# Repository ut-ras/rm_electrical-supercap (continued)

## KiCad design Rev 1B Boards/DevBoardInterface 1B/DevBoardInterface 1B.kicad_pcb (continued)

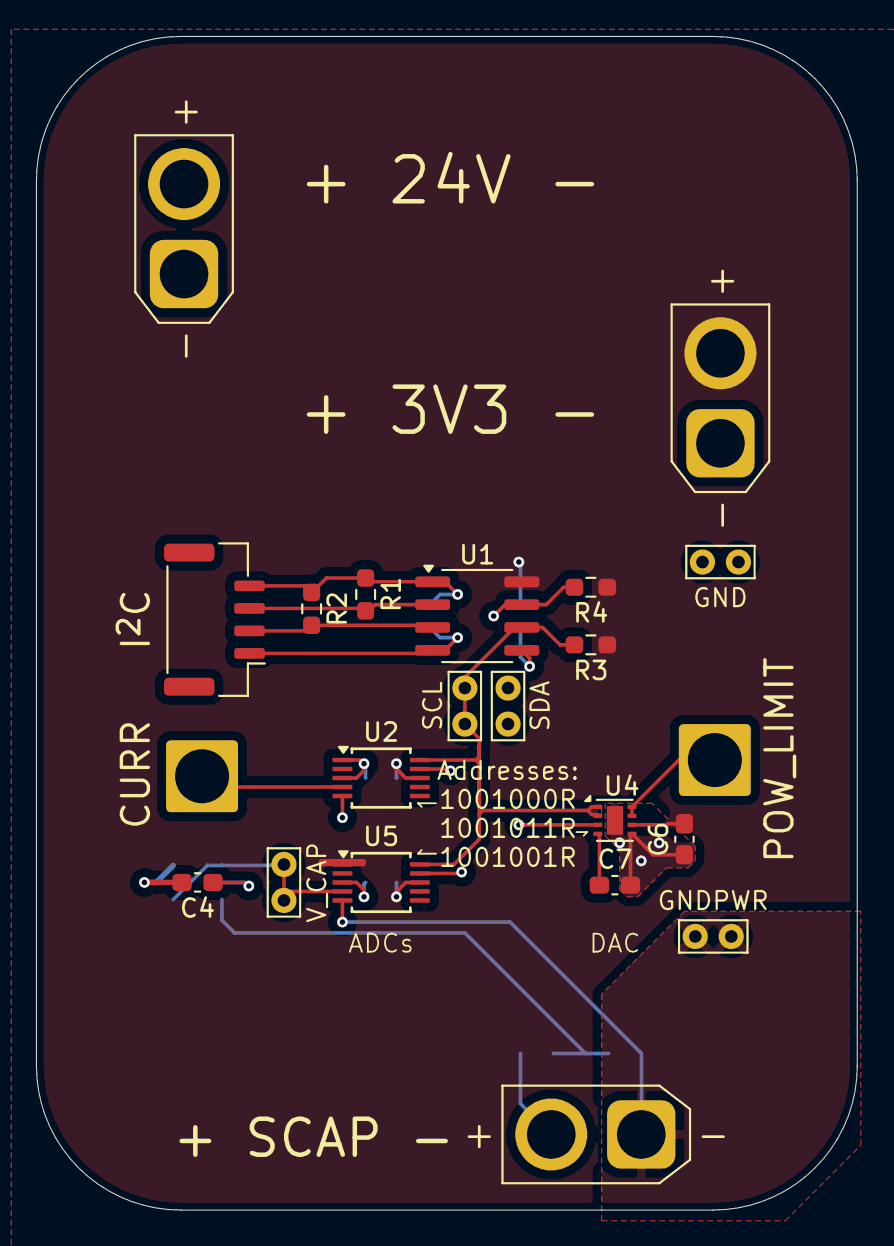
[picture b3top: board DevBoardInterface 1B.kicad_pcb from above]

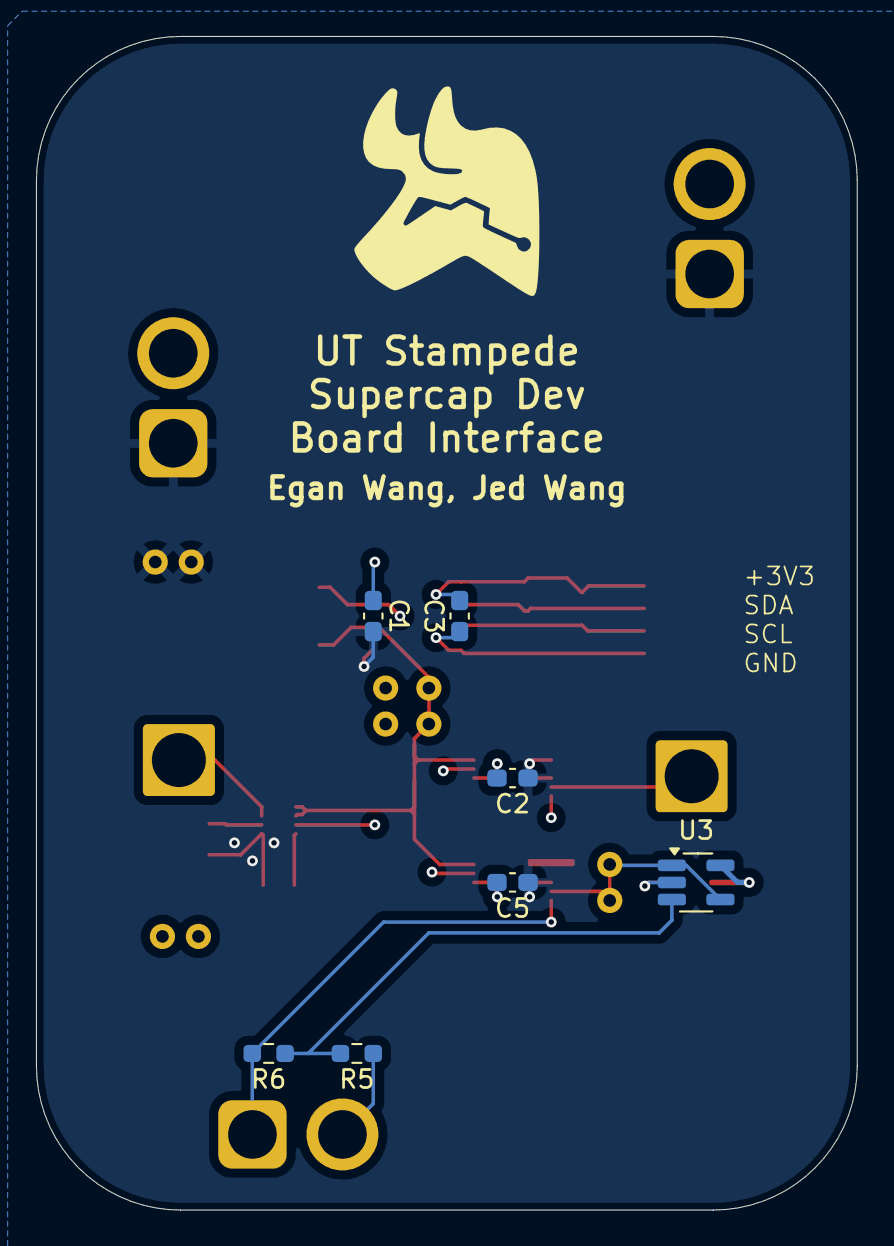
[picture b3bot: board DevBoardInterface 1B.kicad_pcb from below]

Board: 4 copper layers, 45.6 x 65.2 mm, 29 parts (7 on the bottom side), 16 nets.

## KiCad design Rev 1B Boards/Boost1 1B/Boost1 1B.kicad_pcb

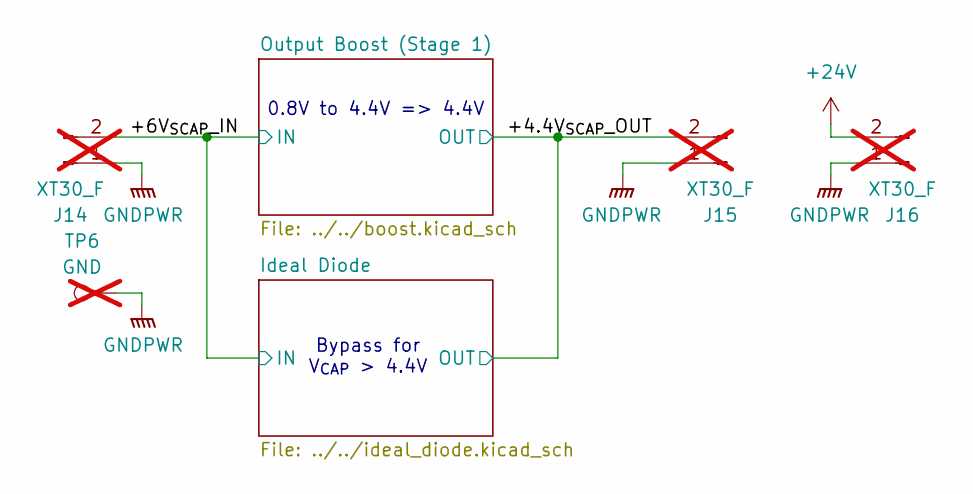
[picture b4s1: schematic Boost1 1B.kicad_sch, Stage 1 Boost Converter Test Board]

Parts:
J14, J15, J16: XT30_F; AMASS_XT30U-F_1x02_P5.0mm_Vertical; not fitted
TP6: GND; TestPoint_Bridge_Pitch2.0mm_Drill0.7mm; not fitted

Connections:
+24V: J16.2; also elsewhere on the board
/+4.4V_{SCAP}_OUT: J15.2; also elsewhere on the board
/+6V_{SCAP}_IN: J14.2; also elsewhere on the board
GNDPWR: J14.1, J15.1, J16.1, TP6.1; also elsewhere on the board

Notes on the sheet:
0.8V to 4.4V => 4.4V
Bypass for V_{CAP} > 4.4V

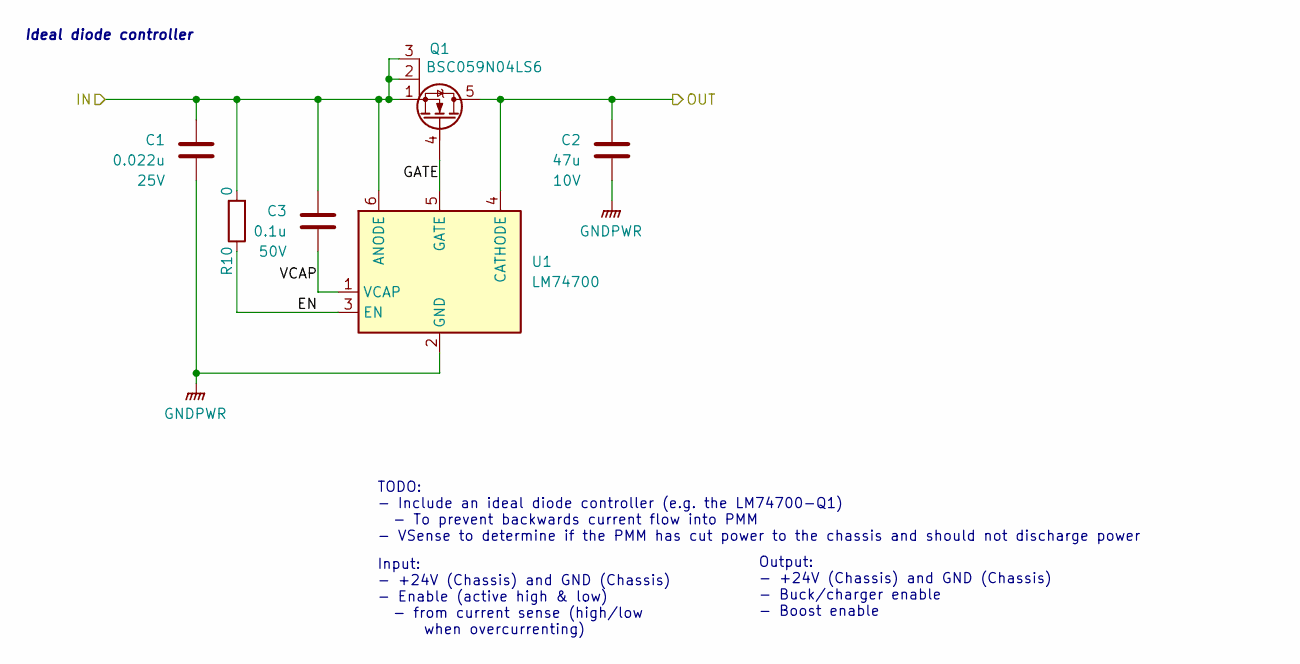
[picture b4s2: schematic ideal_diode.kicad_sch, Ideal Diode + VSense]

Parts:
C1: 0.022u; C_0603_1608Metric_Pad1.08x0.95mm_HandSolder; Voltage Rating 25V; Mouser Part Number 710-885012206067
C2: 47u; C_1206_3216Metric_Pad1.33x1.80mm_HandSolder; Voltage Rating 10V; Mouser Part Number 81-GRM31CR61A476ME5K
C3: 0.1u; C_0603_1608Metric_Pad1.08x0.95mm_HandSolder; Voltage Rating 50V; Mouser Part Number 581-KGM15BR71H104JT
Q1: BSC059N04LS6; Infineon_PG-TDSON-8_6.15x5.15mm; Mouser Part Number 726-BSC059N04LS6ATMA
R10: 0; R_0603_1608Metric_Pad0.98x0.95mm_HandSolder; Mouser Part Number 660-RK73Z1JTTDD
U1: LM74700; SOT-23-6_Handsoldering; Mouser Part Number 595-LM74700QDBVRQ1

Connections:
/+4.4V_{SCAP}_OUT: C2.1, Q1.5 (D), U1.4 (CATHODE); also elsewhere on the board
/+6V_{SCAP}_IN: C1.1, C3.1, Q1.1 (S), Q1.2 (S), Q1.3 (S), R10.2, U1.6 (ANODE); also elsewhere on the board
/Ideal Diode/EN: R10.1, U1.3 (EN)
/Ideal Diode/GATE: Q1.4 (G), U1.5 (GATE)
/Ideal Diode/VCAP: C3.2, U1.1 (VCAP)
GNDPWR: C1.2, C2.2, U1.2 (GND); also elsewhere on the board

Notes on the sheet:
Input: - +24V (Chassis) and GND (Chassis) - Enable (active high & low) - from current sense (high/low when overcurrenting)
Ideal diode controller
Output: - +24V (Chassis) and GND (Chassis) - Buck/charger enable - Boost enable
TODO: - Include an ideal diode controller (e.g. the LM74700-Q1) - To prevent backwards current flow into PMM - VSense to determine if the PMM has cut power to the chassis and should not discharge power

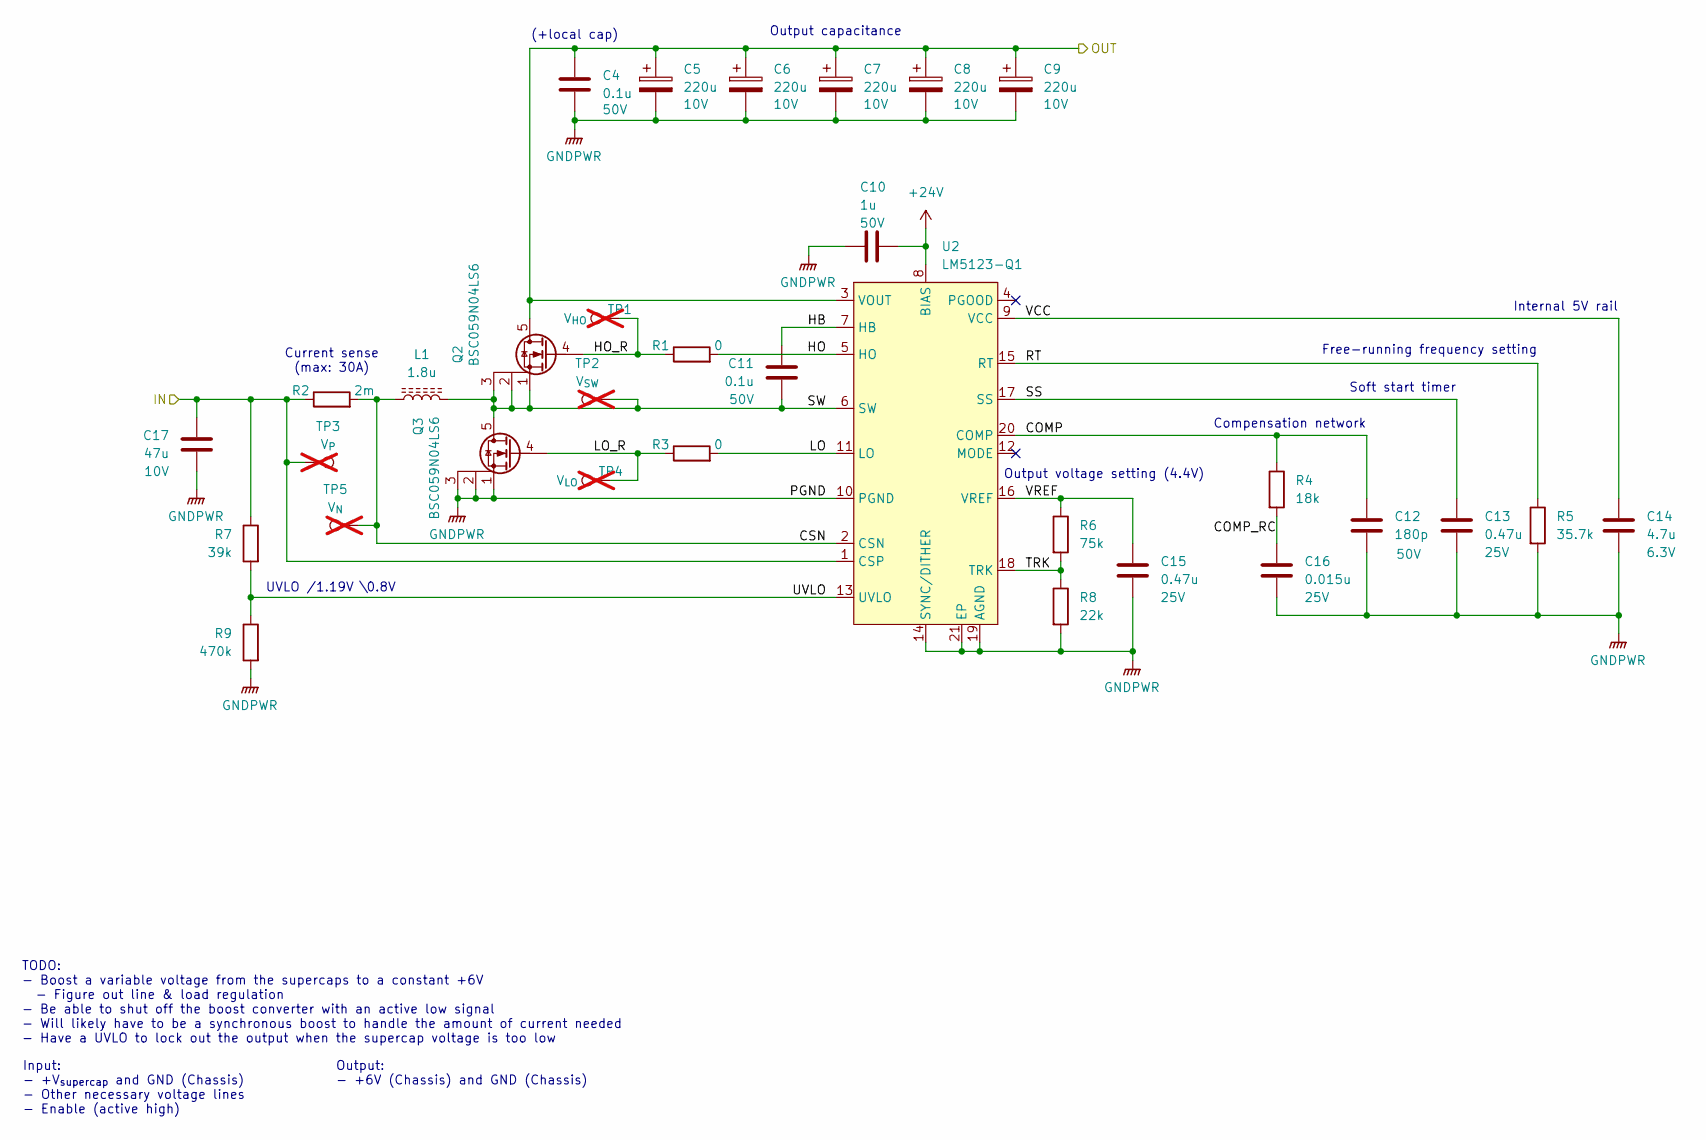
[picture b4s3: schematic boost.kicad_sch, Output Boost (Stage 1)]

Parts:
C4, C11: 0.1u; C_0603_1608Metric_Pad1.08x0.95mm_HandSolder; Voltage Rating 50V; Mouser Part Number 581-KGM15BR71H104JT
C5, C6, C7, C8, C9: 220u; CP_Radial_D6.3mm_P2.50mm; Voltage Rating 10V; Mouser Part Number 80-A750EK227M1AAAE18
C10: 1u; C_0603_1608Metric_Pad1.08x0.95mm_HandSolder; Voltage Rating 50V; Mouser Part Number 963-UMK107BJ105KA-T
C12: 180p; C_0603_1608Metric_Pad1.08x0.95mm_HandSolder; Voltage Rating 50V; Mouser Part Number 603-CC603JPNPO9BN181
C13, C15: 0.47u; C_0603_1608Metric_Pad1.08x0.95mm_HandSolder; Voltage Rating 25V; Mouser Part Number 710-885012106020
C14: 4.7u; C_0603_1608Metric_Pad1.08x0.95mm_HandSolder; Voltage Rating 6.3V; Mouser Part Number 187-CL10A475KQ8NNWC
C16: 0.015u; C_0603_1608Metric_Pad1.08x0.95mm_HandSolder; Voltage Rating 25V; Mouser Part Number 77-VJ0603Y153KXXCBC
C17: 47u; C_1206_3216Metric_Pad1.33x1.80mm_HandSolder; Voltage Rating 10V; Mouser Part Number 81-GRM31CR61A476ME5K
L1: 1.8u; L_Bourns_SRP1245A; Mouser Part Number 652-SRP1265A-1R8M
Q2, Q3: BSC059N04LS6; Infineon_PG-TDSON-8_6.15x5.15mm; Mouser Part Number 726-BSC059N04LS6ATMA
R1, R3: 0; R_0603_1608Metric_Pad0.98x0.95mm_HandSolder; Mouser Part Number 660-RK73Z1JTTDD
R2: 2m; R_2512_6332Metric_Pad1.40x3.35mm_HandSolder; Mouser Part Number 652-CRF2512FZR002ELF
R4: 18k; R_0603_1608Metric_Pad0.98x0.95mm_HandSolder; Mouser Part Number 603-RT0603FRE1318KL
R5: 35.7k; R_0603_1608Metric_Pad0.98x0.95mm_HandSolder; Mouser Part Number 603-RC0603FR-0735K7L
R6: 75k; R_0603_1608Metric_Pad0.98x0.95mm_HandSolder; Mouser Part Number 03-AC0603FR-1075KL
R7: 39k; R_0603_1608Metric_Pad0.98x0.95mm_HandSolder; Mouser Part Number 603-RC0603FR-1339KL
R8: 22k; R_0603_1608Metric_Pad0.98x0.95mm_HandSolder; Mouser Part Number 71-CRCW0603-22K-E3
R9: 470k; R_0603_1608Metric_Pad0.98x0.95mm_HandSolder; Mouser Part Number 660-RN73R1JTD4703B25
TP1: V_{HO}; TestPoint_Pad_1.0x1.0mm; not fitted
TP2: V_{SW}; TestPoint_Pad_1.0x1.0mm; not fitted
TP3: V_{P}; TestPoint_Bridge_Pitch2.0mm_Drill0.7mm; not fitted
TP4: V_{LO}; TestPoint_Pad_1.0x1.0mm; not fitted
TP5: V_{N}; TestPoint_Bridge_Pitch2.0mm_Drill0.7mm; not fitted
U2: LM5123-Q1; Texas_RGP0020H_VQFN-20-1EP_4x4mm_P0.5mm_EP2.4x2.4mm; Mouser Part Number 595-LM51231QRGRRQ1

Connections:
+24V: C10.2, U2.8 (BIAS); also elsewhere on the board
/+4.4V_{SCAP}_OUT: C4.1, C5.1, C6.1, C7.1, C8.1, C9.1, Q2.5 (D), U2.3 (VOUT); also elsewhere on the board
/+6V_{SCAP}_IN: C17.1, R2.1, R7.1, TP3.1, U2.1 (CSP); also elsewhere on the board
/Output Boost (Stage 1)/COMP: C12.1, R4.1, U2.20 (COMP)
/Output Boost (Stage 1)/COMP_RC: C16.1, R4.2
/Output Boost (Stage 1)/CSN: L1.1, R2.2, TP5.1, U2.2 (CSN)
/Output Boost (Stage 1)/HB: C11.1, U2.7 (HB)
/Output Boost (Stage 1)/HO: R1.2, U2.5 (HO)
/Output Boost (Stage 1)/HO_R: Q2.4 (G), R1.1, TP1.1
/Output Boost (Stage 1)/LO: R3.2, U2.11 (LO)
/Output Boost (Stage 1)/LO_R: Q3.4 (G), R3.1, TP4.1
/Output Boost (Stage 1)/RT: R5.1, U2.15 (RT)
/Output Boost (Stage 1)/SS: C13.1, U2.17 (SS)
/Output Boost (Stage 1)/SW: C11.2, L1.2, Q2.1 (S), Q2.2 (S), Q2.3 (S), Q3.5 (D), TP2.1, U2.6 (SW)
/Output Boost (Stage 1)/TRK: R6.2, R8.1, U2.18 (TRK)
/Output Boost (Stage 1)/UVLO: R7.2, R9.1, U2.13 (UVLO)
/Output Boost (Stage 1)/VCC: C14.1, U2.9 (VCC)
/Output Boost (Stage 1)/VREF: C15.1, R6.1, U2.16 (VREF)
GNDPWR: C4.2, C5.2, C6.2, C7.2, C8.2, C9.2, C10.1, C12.2, C13.2, C14.2, C15.2, C16.2, C17.2, Q3.1 (S), Q3.2 (S), Q3.3 (S), R5.2, R8.2, R9.2, U2.10 (PGND), U2.14 (SYNC/DITHER), U2.19 (AGND), U2.21 (EP); also elsewhere on the board

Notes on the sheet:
UVLO /1.19V \0.8V
Output voltage setting (4.4V)
Free-running frequency setting
Current sense (max: 30A)
Soft start timer
Compensation network
TODO: - Boost a variable voltage from the supercaps to a constant +6V - Figure out line & load regulation - Be able to shut off the boost converter with an active low signal - Will likely have to be a synchronous boost to handle the amount of current needed - Have a UVLO to lock out the output when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
Output: - +6V (Chassis) and GND (Chassis)
(+local cap)
Internal 5V rail
Output capacitance
Input: - +V_{supercap} and GND (Chassis) - Other necessary voltage lines - Enable (active high)

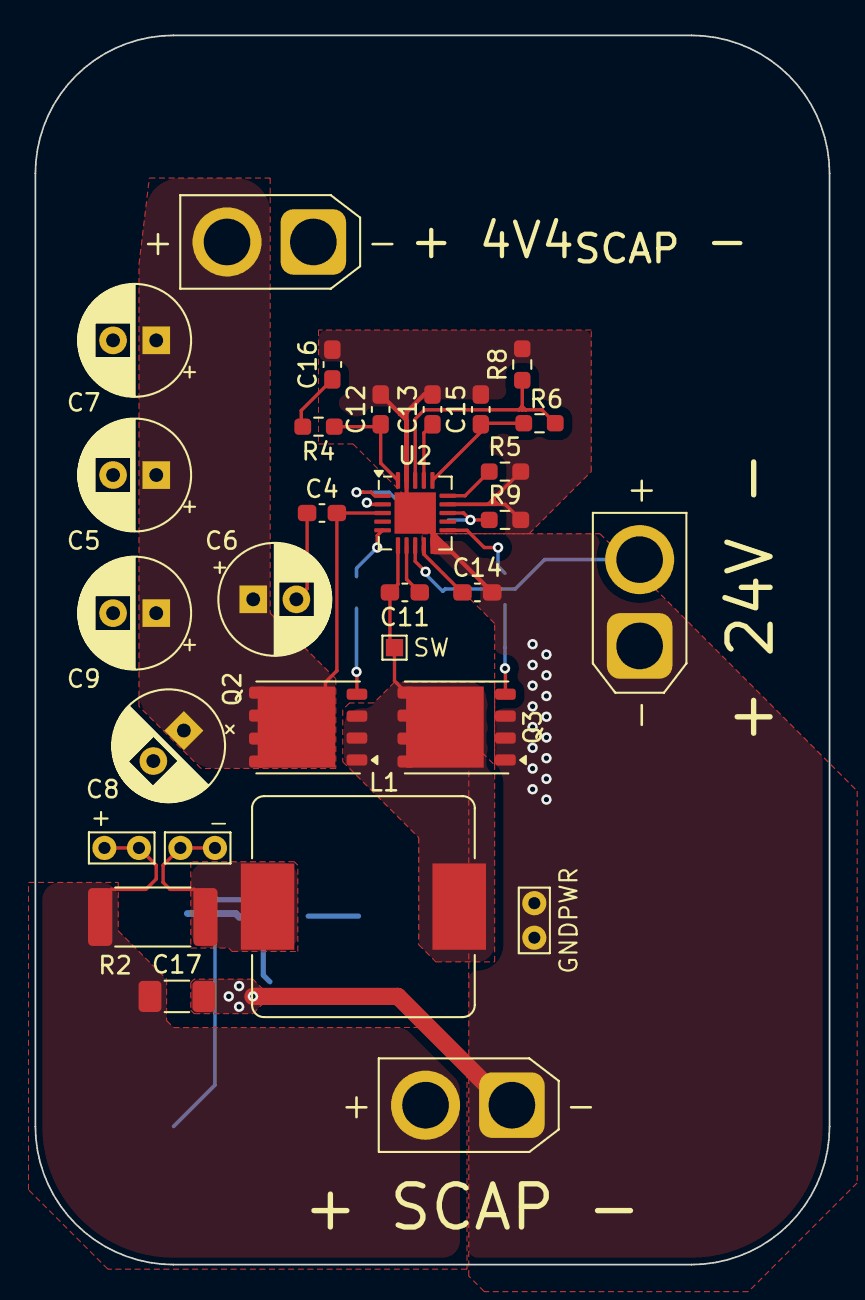
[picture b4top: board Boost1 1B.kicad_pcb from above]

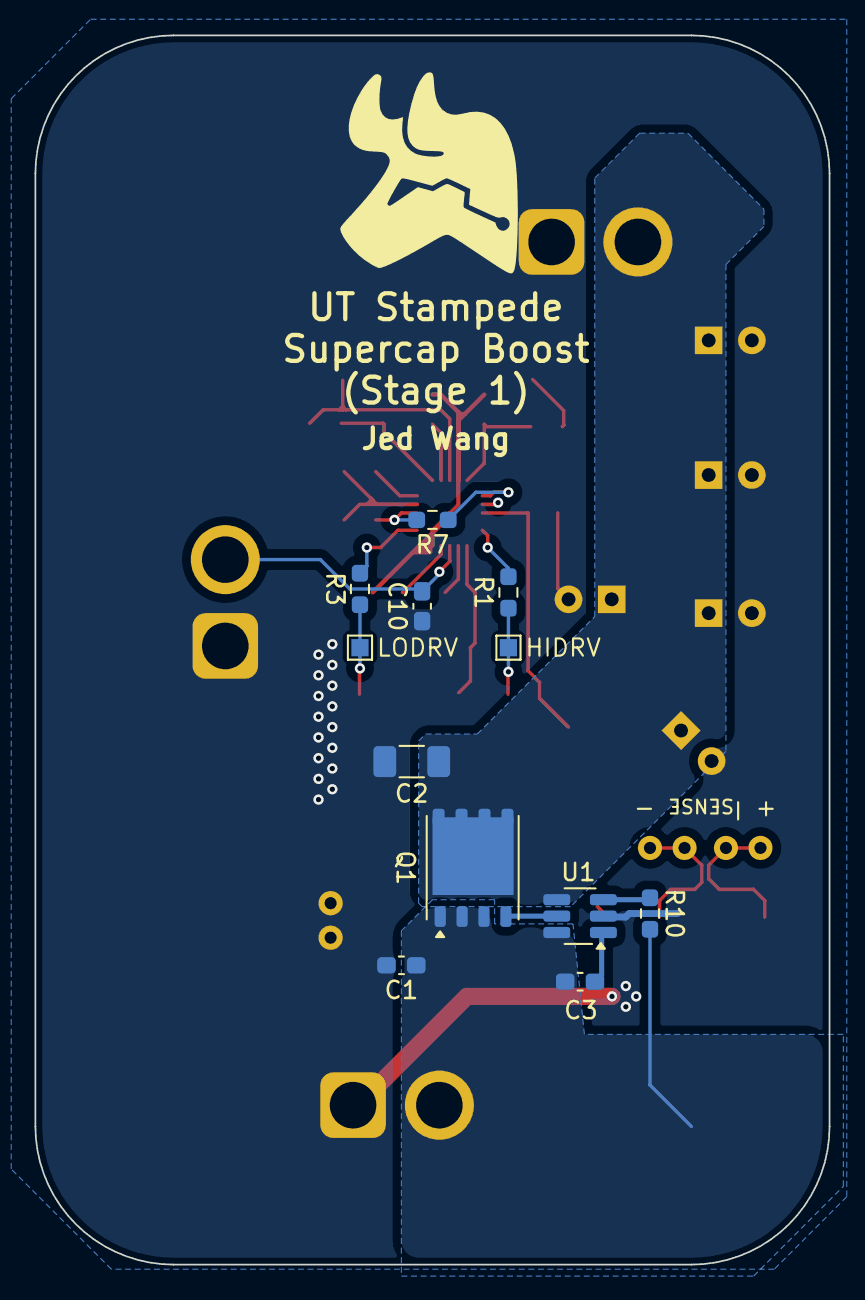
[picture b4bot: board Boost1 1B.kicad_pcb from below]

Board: 4 copper layers, 46.0 x 71.2 mm, 42 parts (12 on the bottom side), 22 nets.

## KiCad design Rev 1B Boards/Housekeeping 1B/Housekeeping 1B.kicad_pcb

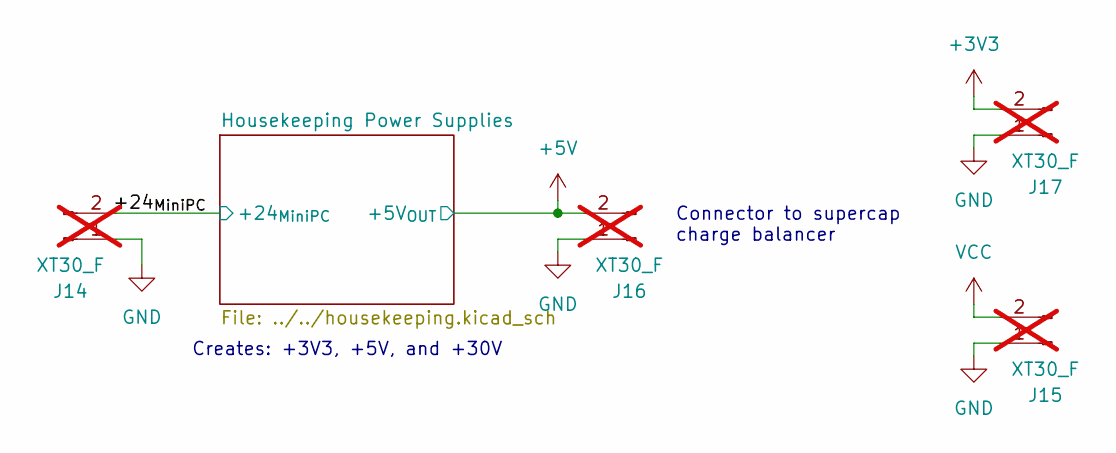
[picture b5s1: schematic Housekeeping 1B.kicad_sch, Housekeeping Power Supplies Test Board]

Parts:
J14, J15, J16, J17: XT30_F; AMASS_XT30U-F_1x02_P5.0mm_Vertical; not fitted

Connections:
+3V3: J17.2; also elsewhere on the board
+5V: J16.2; also elsewhere on the board
/+24_{MiniPC}: J14.2; also elsewhere on the board
GND: J14.1, J15.1, J16.1, J17.1; also elsewhere on the board
VCC: J15.2; also elsewhere on the board

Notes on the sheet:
Creates: +3V3, +5V, and +30V
Connector to supercap charge balancer

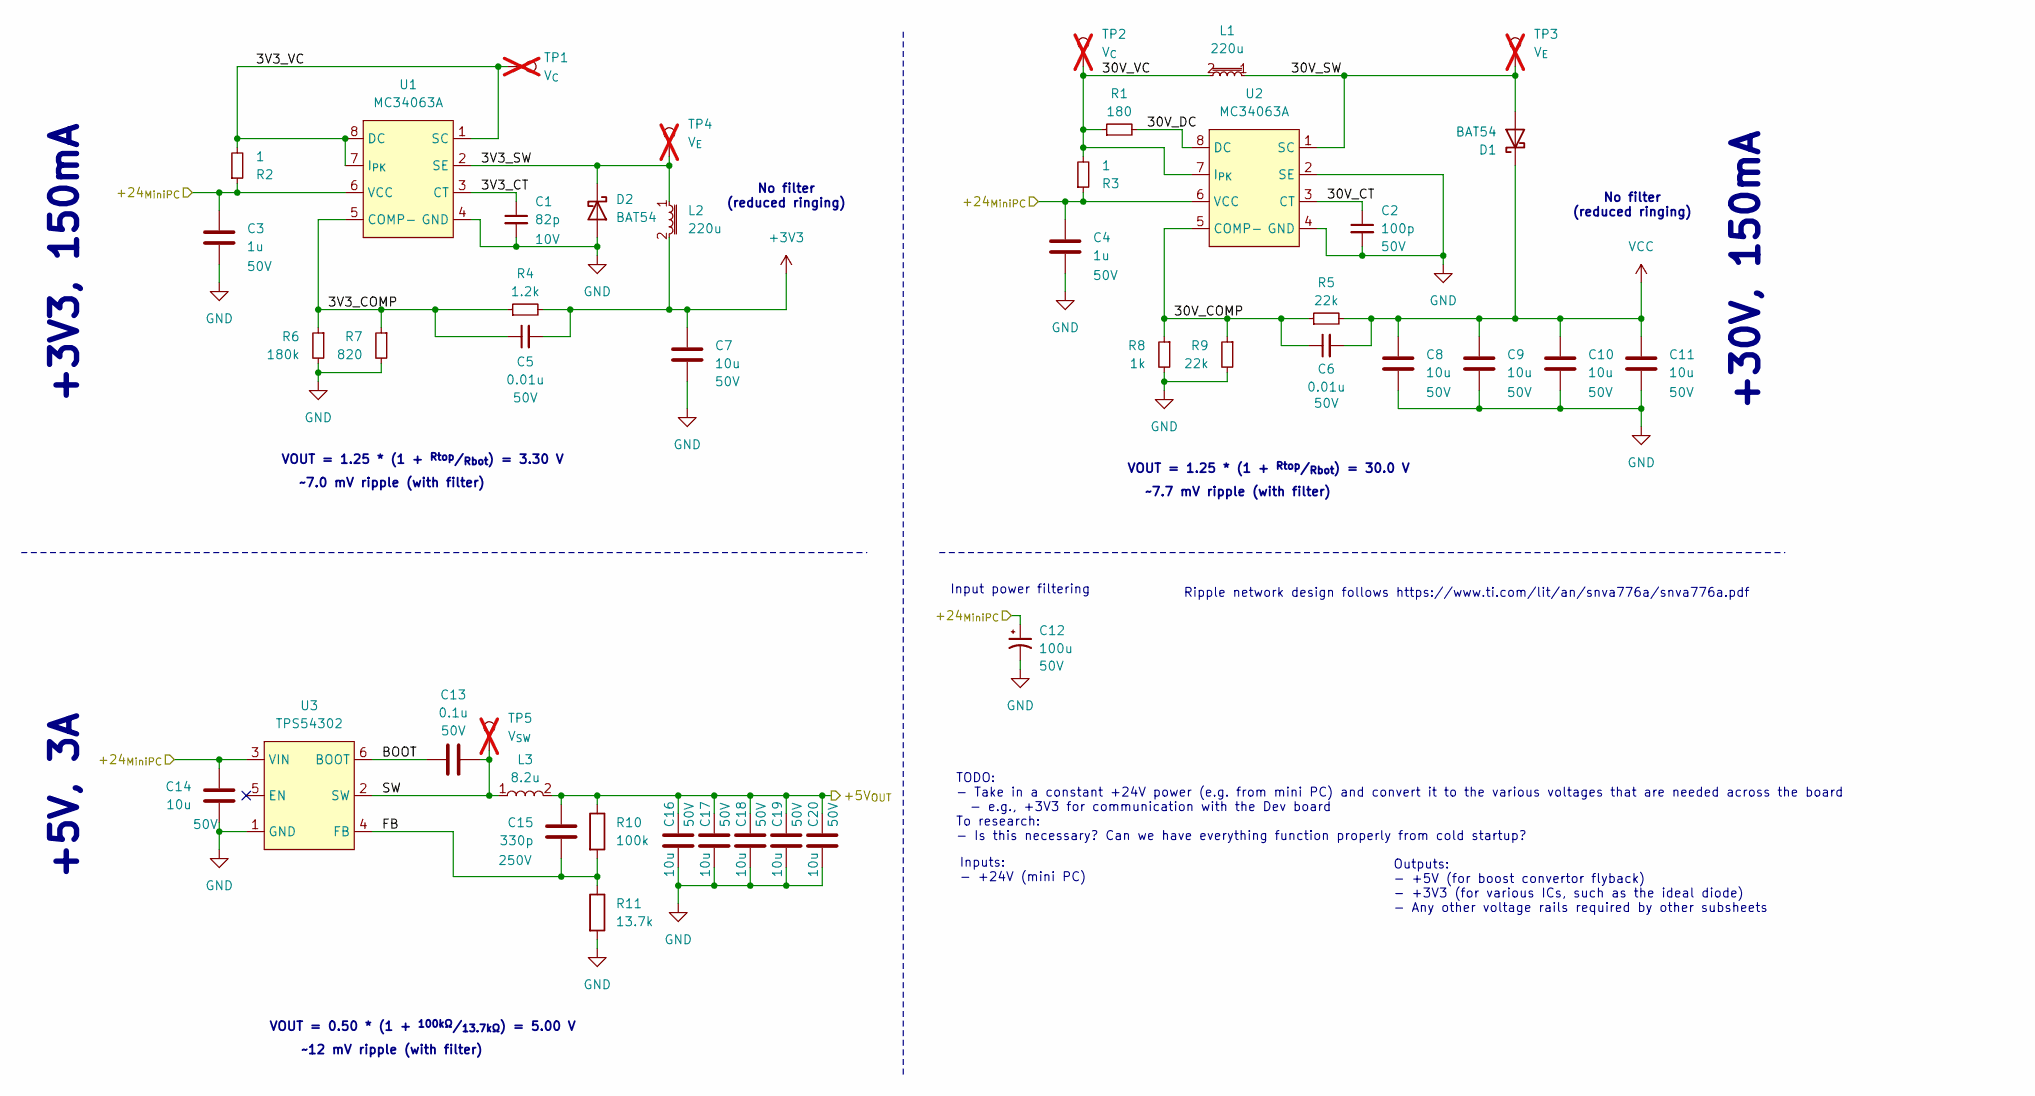
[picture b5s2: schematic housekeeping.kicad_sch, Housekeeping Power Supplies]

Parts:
C1: 82p; C_0603_1608Metric_Pad1.08x0.95mm_HandSolder; Voltage Rating 10V; Mouser Part Number 791-0603N820J100CT
C2: 100p; C_0603_1608Metric_Pad1.08x0.95mm_HandSolder; Voltage Rating 50V; Mouser Part Number 77-VJ0603A101KXACBC
C3, C4: 1u; C_0603_1608Metric_Pad1.08x0.95mm_HandSolder; Voltage Rating 50V; Mouser Part Number 963-UMK107BJ105KA-T
C5, C6: 0.01u; C_0603_1608Metric_Pad1.08x0.95mm_HandSolder; Voltage Rating 50V; Mouser Part Number 187-CL10B103KC8NNNC
C7, C8, C9, C10, C11, C14, C16, C17, C18, C19, C20: 10u; C_1206_3216Metric_Pad1.33x1.80mm_HandSolder; Voltage Rating 50V; Mouser Part Number 187-CL31A106KBHNNNE
C12: 100u; CP_Radial_D8.0mm_P3.50mm; Voltage Rating 50V; Mouser Part Number 710-860010674014
C13: 0.1u; C_0603_1608Metric_Pad1.08x0.95mm_HandSolder; Voltage Rating 50V; Mouser Part Number 581-KGM15BR71H104JT
C15: 330p; C_0603_1608Metric_Pad1.08x0.95mm_HandSolder; Voltage Rating 250V; Mouser Part Number 791-0805N331J251CT
D1, D2: BAT54; SOT-23_Handsoldering; Mouser Part Number 241-BAT54_R1_00001
L1, L2: 220u; ASPIAIGS6055221MT; Mouser Part Number 815-ASPIAIGS6055221T
L3: 8.2u; L_10.4x10.4_H4.8; Mouser Part Number 704-DR1050-8R2-R
R1: 180; R_0805_2012Metric_Pad1.20x1.40mm_HandSolder; Mouser Part Number 667-ERJ-P06J181V
R2, R3: 1; R_0603_1608Metric_Pad0.98x0.95mm_HandSolder; Mouser Part Number 652-CR0603-F/1R00ELF
R4: 1.2k; R_0603_1608Metric_Pad0.98x0.95mm_HandSolder; Mouser Part Number 603-RT0603DRD071K2L
R5, R9: 22k; R_0603_1608Metric_Pad0.98x0.95mm_HandSolder; Mouser Part Number 71-CRCW0603-22K-E3
R6: 180k; R_0603_1608Metric_Pad0.98x0.95mm_HandSolder; Mouser Part Number 603-RT0603DRE07180KL
R7: 820; R_0603_1608Metric_Pad0.98x0.95mm_HandSolder; Mouser Part Number 667-ERA-3AEB821V
R8: 1k; R_0603_1608Metric_Pad0.98x0.95mm_HandSolder; Mouser Part Number 660-RN73R1JTD1001F50
R10: 100k; R_0603_1608Metric_Pad0.98x0.95mm_HandSolder; Mouser Part Number 660-RN73H1JTD1003D25
R11: 13.7k; R_0603_1608Metric_Pad0.98x0.95mm_HandSolder; Mouser Part Number 603-AC0603FR-0713K7L
TP1, TP2: V_{C}; TestPoint_Bridge_Pitch2.0mm_Drill0.7mm; not fitted
TP3, TP4: V_{E}; TestPoint_Pad_1.0x1.0mm; not fitted
TP5: V_{SW}; TestPoint_Bridge_Pitch2.0mm_Drill0.7mm; not fitted
U1, U2: MC34063A; SOIC-8_3.9x4.9mm_P1.27mm; Mouser Part Number 595-MC34063ADR
U3: TPS54302; SOT-23-6_Handsoldering; Mouser Part Number 595-TPS54302DDCR

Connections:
+3V3: C5.2, C7.1, L2.2, R4.2; also elsewhere on the board
+5V: C15.1, C16.1, C17.1, C18.1, C19.1, C20.1, L3.2, R10.1; also elsewhere on the board
/+24_{MiniPC}: C3.1, C4.1, C12.1, C14.1, R2.1, R3.1, U1.6 (VCC), U2.6 (VCC), U3.3 (VIN); also elsewhere on the board
/Housekeeping Power Supplies/3V3_COMP: C5.1, R4.1, R6.1, R7.1, U1.5 (COMP-)
/Housekeeping Power Supplies/3V3_CT: C1.1, U1.3 (CT)
/Housekeeping Power Supplies/3V3_SW: D2.3 (K), L2.1, TP4.1, U1.2 (SE)
/Housekeeping Power Supplies/3V3_VC: R2.2, TP1.1, U1.1 (SC), U1.7 (I_{PK}), U1.8 (DC)
/Housekeeping Power Supplies/30V_COMP: C6.1, R5.1, R8.1, R9.1, U2.5 (COMP-)
/Housekeeping Power Supplies/30V_CT: C2.1, U2.3 (CT)
/Housekeeping Power Supplies/30V_DC: R1.2, U2.8 (DC)
/Housekeeping Power Supplies/30V_SW: D1.1 (A), L1.1, TP3.1, U2.1 (SC)
/Housekeeping Power Supplies/30V_VC: L1.2, R1.1, R3.2, TP2.1, U2.7 (I_{PK})
/Housekeeping Power Supplies/BOOT: C13.1, U3.6 (BOOT)
/Housekeeping Power Supplies/FB: C15.2, R10.2, R11.1, U3.4 (FB)
/Housekeeping Power Supplies/SW: C13.2, L3.1, TP5.1, U3.2 (SW)
GND: C1.2, C2.2, C3.2, C4.2, C7.2, C8.2, C9.2, C10.2, C11.2, C12.2, C14.2, C16.2, C17.2, C18.2, C19.2, C20.2, D2.1 (A), R6.2, R7.2, R8.2, R9.2, R11.2, U1.4 (GND), U2.2 (SE), U2.4 (GND), U3.1 (GND); also elsewhere on the board
VCC: C6.2, C8.1, C9.1, C10.1, C11.1, D1.3 (K), R5.2; also elsewhere on the board

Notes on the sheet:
~12 mV ripple (with filter)
+5V, 3A
+3V3, 150mA
No filter (reduced ringing)
Outputs: - +5V (for boost convertor flyback) - +3V3 (for various ICs, such as the ideal diode) - Any other voltage rails required by other subsheets
VOUT = 1.25 * (1 + ^{Rtop}/_{Rbot}) = 30.0 V
Inputs: - +24V (mini PC)
~7.7 mV ripple (with filter)
TODO: - Take in a constant +24V power (e.g. from mini PC) and convert it to the various voltages that are needed across the board - e.g., +3V3 for communication with the Dev board To research: - Is this necessary? Can we have everything function properly from cold startup?
~7.0 mV ripple (with filter)
Ripple network design follows https://www.ti.com/lit/an/snva776a/snva776a.pdf
Input power filtering
VOUT = 1.25 * (1 + ^{Rtop}/_{Rbot}) = 3.30 V
VOUT = 0.50 * (1 + ^{100kΩ}/_{13.7kΩ}) = 5.00 V
+30V, 150mA

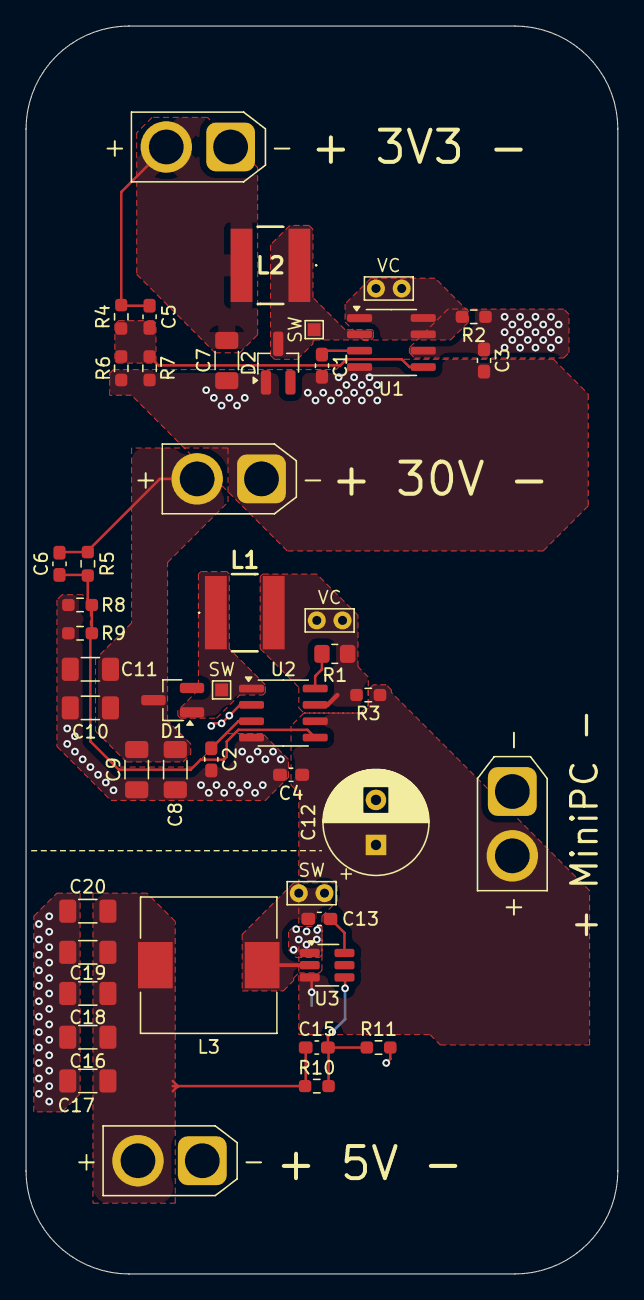
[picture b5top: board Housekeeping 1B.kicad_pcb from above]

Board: 4 copper layers, 46.0 x 97.0 mm, 48 parts (1 on the bottom side), 17 nets.

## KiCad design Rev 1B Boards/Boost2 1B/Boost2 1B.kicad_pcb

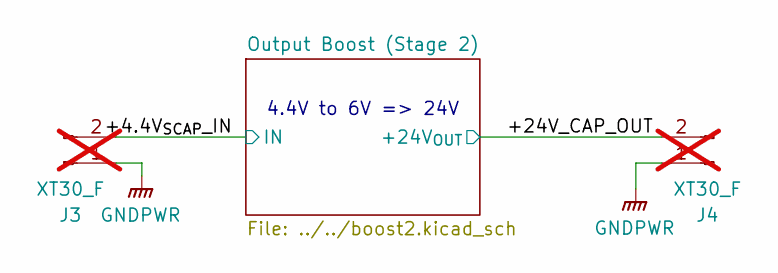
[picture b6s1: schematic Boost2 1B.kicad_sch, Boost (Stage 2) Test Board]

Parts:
J3, J4: XT30_F; AMASS_XT30U-F_1x02_P5.0mm_Vertical; not fitted

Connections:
/+4.4V_{SCAP}_IN: J3.2; also elsewhere on the board
/+24V_CAP_OUT: J4.2; also elsewhere on the board
GNDPWR: J3.1, J4.1; also elsewhere on the board

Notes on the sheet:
4.4V to 6V => 24V

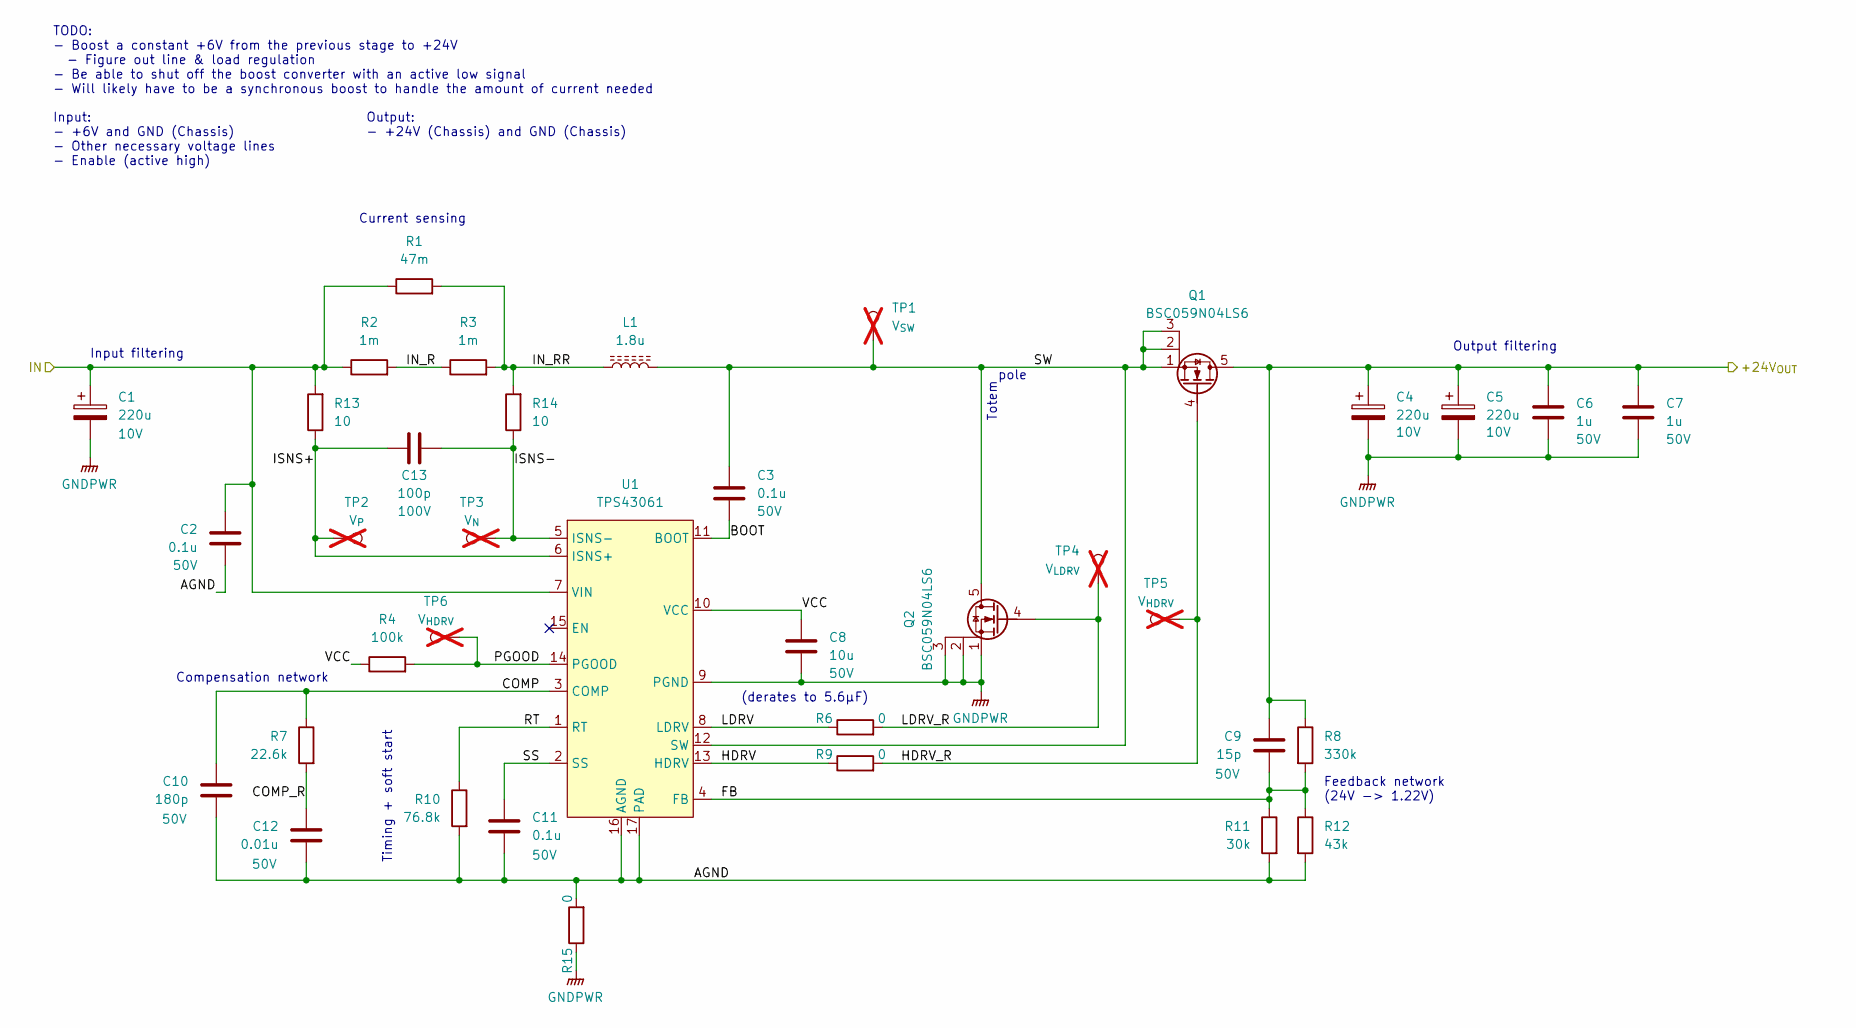
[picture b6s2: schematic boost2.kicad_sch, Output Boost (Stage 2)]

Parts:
C1, C4, C5: 220u; CP_Radial_D6.3mm_P2.50mm; Voltage Rating 10V; Mouser Part Number 80-A750EK227M1AAAE18
C2, C3, C11: 0.1u; C_0603_1608Metric_Pad1.08x0.95mm_HandSolder; Voltage Rating 50V; Mouser Part Number 581-KGM15BR71H104JT
C6, C7: 1u; C_0603_1608Metric_Pad1.08x0.95mm_HandSolder; Voltage Rating 50V; Mouser Part Number 963-UMK107BJ105KA-T
C8: 10u; C_1206_3216Metric_Pad1.33x1.80mm_HandSolder; Voltage Rating 50V; Mouser Part Number 187-CL31A106KBHNNNE
C9: 15p; C_0603_1608Metric_Pad1.08x0.95mm_HandSolder; Voltage Rating 50V; Mouser Part Number 791-0603N150F500CT
C10: 180p; C_0603_1608Metric_Pad1.08x0.95mm_HandSolder; Voltage Rating 50V; Mouser Part Number 603-CC603JPNPO9BN181
C12: 0.01u; C_0603_1608Metric_Pad1.08x0.95mm_HandSolder; Voltage Rating 50V; Mouser Part Number 187-CL10B103KC8NNNC
C13: 100p; C_0603_1608Metric_Pad1.08x0.95mm_HandSolder; Voltage Rating 100V; Mouser Part Number 187-CL10C101JC8NNWC
L1: 1.8u; L_Bourns_SRP1245A; Mouser Part Number 652-SRP1265A-1R8M
Q1, Q2: BSC059N04LS6; Infineon_PG-TDSON-8_6.15x5.15mm; Mouser Part Number 726-BSC059N04LS6ATMA
R1: 47m; R_1206_3216Metric_Pad1.30x1.75mm_HandSolder; Mouser Part Number 603-PE1206FRE470R47L
R2, R3: 1m; R_0612_1632Metric_Pad1.18x3.40mm_HandSolder; Mouser Part Number 71-WFCP06121L000FE66
R4: 100k; R_0603_1608Metric_Pad0.98x0.95mm_HandSolder; Mouser Part Number 660-RN73H1JTD1003D25
R6, R9, R15: 0; R_0603_1608Metric_Pad0.98x0.95mm_HandSolder; Mouser Part Number 660-RK73Z1JTTDD
R7: 22.6k; R_0603_1608Metric_Pad0.98x0.95mm_HandSolder; Mouser Part Number 603-RC0603FR-0722K6L
R8: 330k; R_0603_1608Metric_Pad0.98x0.95mm_HandSolder; Mouser Part Number 603-RT0603DRD07330KL
R10: 76.8k; R_0603_1608Metric_Pad0.98x0.95mm_HandSolder; Mouser Part Number 660-RN73H1JTD7682B25
R11: 30k; R_0603_1608Metric_Pad0.98x0.95mm_HandSolder; Mouser Part Number 660-RN73H1JTD3002B50
R12: 43k; R_0603_1608Metric_Pad0.98x0.95mm_HandSolder; Mouser Part Number 603-RT0603DRD0743KL
R13, R14: 10; R_0603_1608Metric_Pad0.98x0.95mm_HandSolder; Mouser Part Number 594-MCT06030C1009FP5
TP1: V_{SW}; TestPoint_Bridge_Pitch2.0mm_Drill0.7mm; not fitted
TP2: V_{P}; TestPoint_Pad_1.0x1.0mm; not fitted
TP3: V_{N}; TestPoint_Pad_1.0x1.0mm; not fitted
TP4: V_{LDRV}; TestPoint_Pad_1.0x1.0mm; not fitted
TP5: V_{HDRV}; TestPoint_Pad_1.0x1.0mm; not fitted
TP6: V_{HDRV}; TestPoint_Bridge_Pitch2.0mm_Drill0.7mm; not fitted
U1: TPS43061; Texas_S-PWQFN-N16; Mouser Part Number 595-TPS43061RTER

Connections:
/+4.4V_{SCAP}_IN: C1.1, C2.1, R1.1, R2.1, R13.2, U1.7 (VIN); also elsewhere on the board
/+24V_CAP_OUT: C4.1, C5.1, C6.1, C7.1, C9.1, Q1.5 (D), R8.1; also elsewhere on the board
/Output Boost (Stage 2)/AGND: C2.2, C10.2, C11.2, C12.2, R10.2, R11.2, R12.2, R15.2, U1.16 (AGND), U1.17 (PAD)
/Output Boost (Stage 2)/BOOT: C3.2, U1.11 (BOOT)
/Output Boost (Stage 2)/COMP: C10.1, R7.1, U1.3 (COMP)
/Output Boost (Stage 2)/COMP_R: C12.1, R7.2
/Output Boost (Stage 2)/FB: C9.2, R8.2, R11.1, R12.1, U1.4 (FB)
/Output Boost (Stage 2)/HDRV: R9.1, U1.13 (HDRV)
/Output Boost (Stage 2)/HDRV_R: Q1.4 (G), R9.2, TP5.1
/Output Boost (Stage 2)/IN_R: R2.2, R3.1
/Output Boost (Stage 2)/IN_RR: L1.1, R1.2, R3.2, R14.2
/Output Boost (Stage 2)/ISNS+: C13.1, R13.1, TP2.1, U1.6 (ISNS+)
/Output Boost (Stage 2)/ISNS-: C13.2, R14.1, TP3.1, U1.5 (ISNS-)
/Output Boost (Stage 2)/LDRV: R6.1, U1.8 (LDRV)
/Output Boost (Stage 2)/LDRV_R: Q2.4 (G), R6.2, TP4.1
/Output Boost (Stage 2)/PGOOD: R4.2, TP6.1, U1.14 (PGOOD)
/Output Boost (Stage 2)/RT: R10.1, U1.1 (RT)
/Output Boost (Stage 2)/SS: C11.1, U1.2 (SS)
/Output Boost (Stage 2)/SW: C3.1, L1.2, Q1.1 (S), Q1.2 (S), Q1.3 (S), Q2.5 (D), TP1.1, U1.12 (SW)
/Output Boost (Stage 2)/VCC: C8.1, R4.1, U1.10 (VCC)
GNDPWR: C1.2, C4.2, C5.2, C6.2, C7.2, C8.2, Q2.1 (S), Q2.2 (S), Q2.3 (S), R15.1, U1.9 (PGND); also elsewhere on the board

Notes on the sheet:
Input: - +6V and GND (Chassis) - Other necessary voltage lines - Enable (active high)
Timing + soft start
Compensation network
Output: - +24V (Chassis) and GND (Chassis)
Input filtering
Current sensing
pole
Feedback network (24V -> 1.22V)
(derates to 5.6µF)
TODO: - Boost a constant +6V from the previous stage to +24V - Figure out line & load regulation - Be able to shut off the boost converter with an active low signal - Will likely have to be a synchronous boost to handle the amount of current needed
Output filtering
Totem
